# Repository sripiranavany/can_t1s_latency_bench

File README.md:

# CAN over Ethernet Latency Bench

A testbed for measuring latency when **CAN traffic is tunnelled over automotive
Ethernet**, built on Zephyr RTOS and STM32.

The aim is to quantify what it costs, in latency and jitter, to carry CAN frames
across single-pair Ethernet using IEEE 1722 / [Open1722](https://github.com/COVESA/Open1722)
(AVTP CAN encapsulation), compared with a native CAN bus. The matrix of
configurations to compare:

| | Classic CAN | CAN FD |
| --- | --- | --- |
| **10BASE-T1S** (PLCA multidrop) | Current focus | Planned |
| **100BASE-T1** (point-to-point) | Planned | Planned |

```
 CAN node ──CAN──▶ STM32 (Zephyr) ──SPI──▶ LAN8651 ══10BASE-T1S (PLCA)══ LAN8670 ──USB──▶ Linux host
                   bxCAN + OA-TC6           MAC-PHY                         EVB-LAN8670-USB   timestamps / analysis
```

## Technology stack

| Layer | Choice |
| --- | --- |
| RTOS | Zephyr |
| MCU | STM32 NUCLEO-F439ZI (bxCAN, classic CAN 2.0 only). A CAN FD capable MCU (FDCAN) is needed for the FD tests |
| Ethernet | 10BASE-T1S with PLCA, Microchip LAN8651 (MAC-PHY over SPI, OA TC6). 100BASE-T1 planned |
| CAN transport | IEEE 1722 AVTP via Open1722 |
| CAN PHY | MCP2562FD transceiver, PESD2CAN protection |
| Host | Linux (Raspberry Pi / PC) with EVB-LAN8670-USB, `microchip_t1s` driver |

## Status

| Item | State |
| --- | --- |
| SPI link STM32 ↔ Click Shield verified | Done |
| LAN8651 bring-up on Zephyr (direct wiring and Click Shield socket 3) | Done |
| 10BASE-T1S frames received on STM32 and bridged out on CAN1 | Working prototype (fixed CAN ID `0x123`) |
| Linux host PLCA setup (driver build, hotplug automation) | Done |
| Custom CAN SPE carrier PCB | Schematic and layout in progress |
| Open1722 (AVTP CAN) integration | Not started |
| CAN FD tests | Planned, needs an FDCAN-capable board |
| 100BASE-T1 tests | Planned, needs a 100BASE-T1 PHY / board |
| Latency measurement and analysis | Not started |

## Repository layout

| Path | Contents |
| --- | --- |
| [`host-tools/with-click-shield/`](host-tools/with-click-shield/) | Zephyr firmware for the NUCLEO-F439ZI: LAN8651 bring-up, raw-frame RX, CAN bridge. Wiring variants are selected with devicetree overlays |
| [`host-tools/t1s-plca-setup/`](host-tools/t1s-plca-setup/README.md) | udev rules, systemd unit and scripts that put an EVB-LAN8670-USB into a PLCA-configured state on boot and hotplug |
| [`hardware/CAN SPE CARRIER/`](hardware/CAN%20SPE%20CARRIER/README.md) | KiCad project for the carrier board (CAN transceiver + 10BASE-T1S on a Nucleo-144 / click-shield footprint) |
| [`hardware/kicad-files/`](hardware/kicad-files/) | Third-party KiCad parts (MCP2562FD, PESD2CAN) |
| [`docs/`](docs/) | Bring-up notes, see below |

## Documentation

- [Direct LAN8651 ↔ STM32F439ZI wiring](docs/direct-lan8651-stm32f439zi.md): the known-good hardware setup, plus the Click Shield route
- [SPI verification on the Click Shield](docs/spi-verification-click-shield.md): loopback test and pin mapping
- [10BASE-T1S on Linux](docs/t1s-driver-build.md): building the PHY driver and manual PLCA testing
- [Useful links](docs/links): Click Shield and Nucleo-144 datasheets

## Getting started

Prerequisites: a Zephyr SDK and `west` workspace, a NUCLEO-F439ZI, a MikroE
Two-Wire ETH Click (LAN8651), and a Linux host with an EVB-LAN8670-USB.

1. **Host side.** Build the `microchip_t1s` driver and set up PLCA, following
   [`docs/t1s-driver-build.md`](docs/t1s-driver-build.md) and then
   [`host-tools/t1s-plca-setup`](host-tools/t1s-plca-setup/README.md).
2. **Wire the Click board** to the Nucleo as described in
   [`docs/direct-lan8651-stm32f439zi.md`](docs/direct-lan8651-stm32f439zi.md).
3. **Build and flash the firmware:**

   ```bash
   cd host-tools/with-click-shield
   west build -b nucleo_f439zi -p always .
   west flash
   ```

   To use the Click Shield and/or the CAN bridge, stack overlays:

   ```bash
   west build -b nucleo_f439zi -p always . \
       -DEXTRA_DTC_OVERLAY_FILE="click-shield.overlay;can.overlay"
   ```

   The CAN overlay uses PD0 (RX) / PD1 (TX) and needs an external CAN
   transceiver. See the header of [`can.overlay`](host-tools/with-click-shield/can.overlay).

## Notes

- bxCAN on the STM32F4 is classic CAN 2.0 only (8-byte payload, 1 Mbit/s max). There is no CAN FD on this part, so the CAN FD runs will need a different MCU with FDCAN.
- Click Shield socket 3 needs its logic-level switch set to 3V3.
- `_backup/` holds an older EVB-LAN8670 setup guide kept for reference.

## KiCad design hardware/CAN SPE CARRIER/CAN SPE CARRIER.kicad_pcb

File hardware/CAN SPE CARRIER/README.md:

# CAN SPE CARRIER – PCB Routing Guide (for KiCad beginners)

This file explains **how the board was routed**, **what you are looking at when you open it in KiCad**,
and **what to check before sending it to a manufacturer**.

> **Fixed parts:** J3, J4, J5 and J6 are the click-shield / mainboard headers. Their positions were
> **not allowed to change**, so everything else was placed and routed around them.

---

## 1. Files in this folder

| File | What it is |
|---|---|
| `CAN SPE CARRIER.kicad_pro` | Project file (design rules, net classes) |
| `CAN SPE CARRIER.kicad_sch` | Schematic |
| `CAN SPE CARRIER.kicad_pcb` | The routed board – **open this one** |
| `CAN SPE CARRIER-backups/` | Automatic zip backups. `…-before-routing.kicad_pcb` is your board **before** the re-route |
| `_autosave-*.kicad_pcb` | KiCad autosave, safe to ignore/delete |
| `~*.lck` | Lock files from an earlier session. KiCad may warn "file is open" – if KiCad is not running, click *Ignore/Open anyway* or delete the `.lck` files |

---

## 2. Quick glossary

- **Net** – a set of pads that must be electrically connected (e.g. `GND`, `+3V3`, `/SPI_SCK`).
- **Track / trace** – a copper line that carries a net.
- **Via** – a plated hole that moves a track from one copper layer to the other.
- **Pad** – the copper spot on a part where you solder.
- **Zone / pour** – a big filled copper area (here: ground).
- **Net class** – a group of nets that share rules (track width, clearance). Here: `Default` and `Power`.
- **Ratsnest** – thin straight lines in KiCad showing connections that are *not yet routed*. A finished board has none.
- **DRC** – Design Rule Check; KiCad's automatic error checker.

---

## 3. Why the colours look different in KiCad

KiCad draws each copper layer in its own colour. If you opened the board and everything "changed colour", this is normal:

| Colour (default theme) | Layer | Meaning |
|---|---|---|
| **Red** | `F.Cu` | Front copper (top side) |
| **Green/Blue** | `B.Cu` | Back copper (bottom side) |
| Light red/green haze | GND zones | The ground pour on each layer |
| Yellow lines | `Edge.Cuts` | Board outline |

Tips:
- **Active layer is bright, the other layers are dimmed.** Press `PgUp` / `PgDn`, or click a layer in the
  right-hand *Appearance* panel, and the colours swap emphasis. That is why the board looks different each time.
- *Appearance* panel → **Layers** → *Colour* swatch lets you change any colour.
- **Highlight a net:** press `` ` `` (backtick) or use *Route → Highlight Net* (shortcut `` ` ``)
  and click a track. Everything on that net lights up, and everything else dims. This is the **best way to
  understand the routing**.
- *Appearance* → **Objects** → untick *Zones* (or set *Zone fill* opacity low) to hide the ground pour so you
  can see the tracks clearly.
- *Appearance* → **Nets** lets you show/hide or recolour individual nets.
- Press `B` to refill zones after any change; `Ctrl+B` clears the fill.
- **Show the whole board:** `Home`. **Zoom:** scroll wheel. **Measure:** `Ctrl+Shift+M`.

---

## 4. Board overview

```
                    TOP EDGE  (y ≈ 46…50 mm)
   J5 (left, x≈22)  ─────────────────────────  J6 (right, x≈85)
   click-shield side                              mainboard side
        │   J3 (x≈59, y≈73)    J4 (x≈59, y≈50)    │
        │   TP1 D1 R3 R2 C4  ← 3V3 loads           │
        │   C3  TP2          ← 5V cap              │
        │                                          │
        │   C2 C1  U2 (MCP2562 CAN transceiver)    │
        │                       D2  R1  J2   J1    │
        └──────────── BOTTOM (y ≈ 140 mm) ─────────┘
```

Roughly 69 × 93 mm board, 2 copper layers.

Signal flow in one sentence: **mainboard (J6→J4) and click shield (J5→J3) feed the CAN transceiver U2, whose CANH/CANL
outputs go through the protection diode D2 and termination R1 to the screw terminal J1 (and jumper J2).**

---

## 5. Routing, net by net

Track widths: signals **0.25 mm**, power **0.5 mm**, short stubs near pads 0.3 mm.
Clearance everywhere: **0.2 mm**. Vias: **0.6 mm pad / 0.3 mm drill**.

### 5.1 SPI bus (J5 → J3)
| Net | Layer | How |
|---|---|---|
| `/SPI_SCK` | F.Cu (top) | Part of a parallel bundle |
| `/SPI_MISO` | F.Cu (top) | Part of a parallel bundle |
| `/SPI_CS` | F.Cu (top) | Part of a parallel bundle |
| `/SPI_MOSI` | **B.Cu (bottom)** | Runs underneath the bundle |

- The three top-layer signals run side by side using **45° bends** (no sharp 90° corners), keeping the same spacing.
- MOSI was put on the **other layer** so it never has to cross the others → **no vias needed** for SPI.

### 5.2 Mainboard signals (J6 → J4): `/MB_INT`, `/MB_SCL`, `/MB_SDA`
- All on **F.Cu**, running along the **top edge** (above the headers).
- Each one sits at a **different height ("staggered levels")** so the lines never cross each other.
- In KiCad: highlight `/MB_INT` and you will see a long horizontal line at y ≈ 47.2 mm joining J6 to J4.

### 5.3 `/MB_RST`
- On **B.Cu** (bottom). It goes **around the right end of J3** and then up into pin **J3.2**.
- Using the back layer avoids all the top-layer signals.

### 5.4 +3V3 power
- A **0.5 mm trunk on F.Cu** from **J5.16** to **J3.7**, with short branches to the nearby 3.3 V parts
  (R2, R3, D1/LED resistor, C4, TP1).
- **One via** drops the net to **B.Cu**, and a short bottom run feeds **U2** (CAN transceiver VIO) and **C1** (100 nF decoupling).

### 5.5 +5V power
- A **0.5 mm trunk on F.Cu** to **J4.7** and **C3** (5 V bulk cap, placed right beside the trunk).
- A **B.Cu run goes straight down** to **U2** (VCC) and **C2** (100 nF decoupling).
- One via connects the top trunk to the bottom run.

### 5.6 CAN logic: `/CAN_TX`, `/CAN_RX`
- Direct, short **F.Cu** tracks from the J5 header down to U2 (TXD / RXD pins). No vias.

### 5.7 CAN bus: CANH / CANL
These are named `Net-(J1-Pin_1)` and `Net-(J1-Pin_2)` in KiCad (no custom label).
- Routed as a **matched pair** on F.Cu above J1: same layer, same length-ish, constant spacing.
- They are arranged so they **do not cross** each other on the way to D2 (ESD protection), R1 (120 Ω termination) and J1.
- Good practice for CAN: keep the pair together and symmetrical – that is what was done here.

### 5.8 Ground (GND)
- A **ground pour (zone) on both F.Cu and B.Cu** covering the whole board.
- Every GND pad connects into the pour (thermal-relief spokes: 0.4 mm bridges, 0.3 mm gap).
- **Vias join the top and bottom pours** so both are one ground. (The board currently has only 2 GND vias – see §8.)
- Because of the pour, you do not see individual GND tracks; ground is "everywhere there is no other signal".

---

## 6. Parts that were moved (none of J3–J6)

R1, R2, R3, C1, C3, C4, D1, D2, J2, TP1, TP2.

Why:
- **3.3 V loads** (R2, R3, C4, D1, C1) were moved next to the 3V3 trunk → shorter, simpler power tracks.
- **5 V cap** (C3) moved beside the 5V trunk.
- **D2, R1, J2** were moved **below J1**, because the body of the J1 screw terminal covered their old position.
- ⚠ **Check:** if the wires enter J1 from the **top** side, make sure D2, R1 and J2 don't block the wire entry.

---

## 7. Other changes made
- Added a **`Power` net class** in the project: **0.5 mm** tracks for `+5V` and `+3V3`
  (Board Setup → Design Rules → Net Classes).
- Old routing removed (it had 5 warnings, 8 unconnected items, dangling B.Cu tracks with no vias,
  long diagonal runs and no ground pour) and re-routed from scratch.
- Previous board saved as `CAN SPE CARRIER-backups/CAN SPE CARRIER-before-routing.kicad_pcb`
  (use *File → Restore Local Backup…* or just open that file).

---

## 8. How to review it yourself (step by step)

1. Open `CAN SPE CARRIER.kicad_pcb` (from the project, via the PCB Editor).
2. Press `B` to refill zones.
3. Run **Inspect → Design Rules Checker → Run DRC**. Expected: 0 errors, 0 unconnected items.
   (Tick *"Test for parity between PCB and schematic"* too.)
4. Walk through the nets: press `` ` `` on each track and read the list in §5.
5. Use **View → 3D Viewer** (`Alt+3`) to check that parts don't collide with J1.
6. Use *Appearance → Layers* to view only `F.Cu`, then only `B.Cu`.

### Things to improve / double-check
- **Stitching vias:** only 2 GND vias exist. Adding a few more near the edges and next to the signal vias
  (*Place → Via*, set net to `GND`) improves return-current paths between the two ground pours.
- **Check the current rating:** 0.5 mm copper at 1 oz handles roughly 1 A; verify this is enough for your 3V3 and 5V loads.
- **Fab capabilities:** the design uses 0.2 mm clearance, 0.25 mm signal tracks and 0.6/0.3 mm vias.
  Confirm your manufacturer allows these (most standard 2-layer services do).
- **Lock files:** delete `~*.lck` if KiCad keeps warning you.

---

## 9. Handy KiCad shortcuts (PCB Editor)

| Key | Action |
|---|---|
| `` ` `` | Highlight net under cursor |
| `B` | Refill all zones |
| `X` | Start routing a track |
| `V` | Place a via while routing (also switches layer) |
| `D` | Drag a track |
| `M` / `G` | Move / Grab (keeps connections) |
| `Del` | Delete selected |
| `Ctrl+Z` | Undo |
| `PgUp/PgDn` | Switch active copper layer |
| `Alt+3` | 3D viewer |
| `Ctrl+Shift+M` | Measure tool |
| `Home` | Zoom to fit |

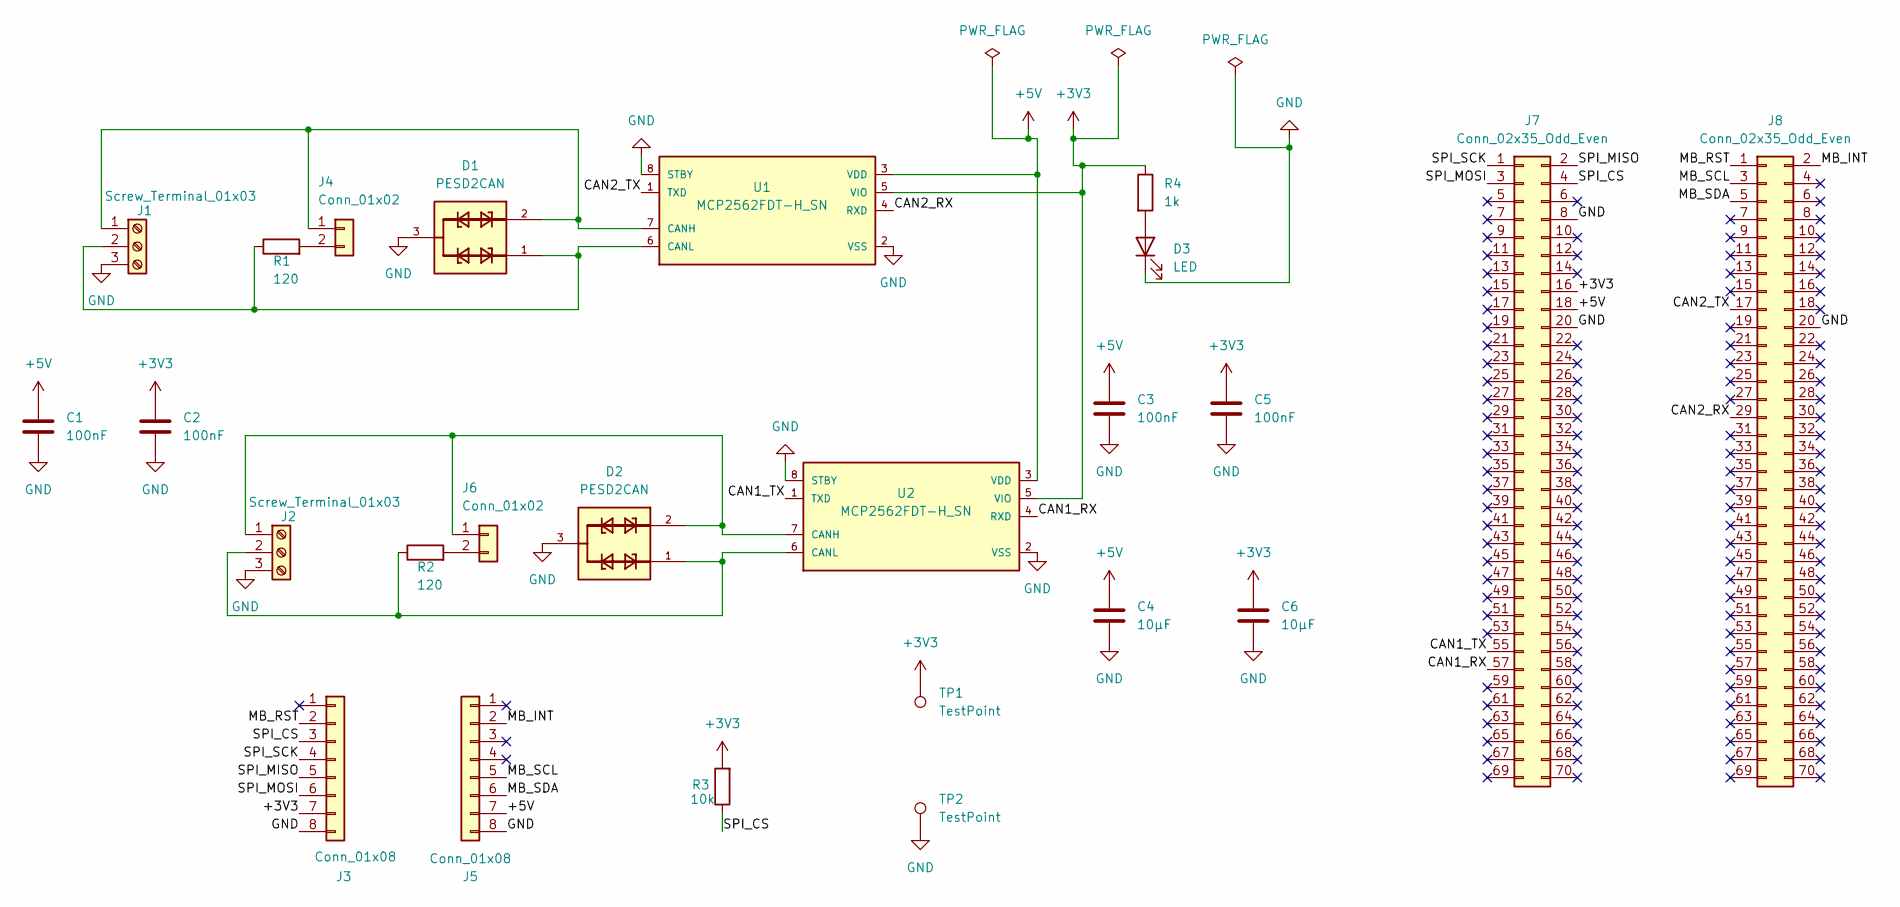
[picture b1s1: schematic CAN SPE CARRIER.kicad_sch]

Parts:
C1, C2, C3, C5: 100nF; C_0805_2012Metric
C4, C6: 10µF; C_0805_2012Metric
D1, D2: PESD2CAN; SOT-23
D3: LED; LED_0805_2012Metric
J1, J2: Screw_Terminal_01x03; TerminalBlock_Phoenix_MKDS-1,5-3-5.08_1x03_P5.08mm_Horizont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
J3, J5: Conn_01x08; PinSocket_1x08_P2.54mm_Vertical
J4, J6: Conn_01x02; PinHeader_1x02_P2.54mm_Vertical
J7, J8: Conn_02x35_Odd_Even; PinSocket_2x35_P2.54mm_Vertical
R1, R2: 120; R_0805_2012Metric
R3: 10k; R_0805_2012Metric
R4: 1k; R_0805_2012Metric
TP1, TP2: TestPoint; TestPoint_Pad_D1.5mm
U1, U2: MCP2562FDT-H_SN; SOIC-8_3.9x4.9mm_P1.27mm

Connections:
+3V3: C2.1, C5.1, C6.1, J3.7, J7.16, R3.2, R4.1, TP1.1 (1_1), U1.5 (VIO), U2.5 (VIO)
+5V: C1.1, C3.1, C4.1, J5.7, J7.18, U1.3 (VDD), U2.3 (VDD)
/CAN1_RX: J7.57, U2.4 (RXD)
/CAN1_TX: J7.55, U2.1 (TXD)
/CAN2_RX: J8.29, U1.4 (RXD)
/CAN2_TX: J8.17, U1.1 (TXD)
/MB_INT: J5.2, J8.2
/MB_RST: J3.2, J8.1
/MB_SCL: J5.5, J8.3
/MB_SDA: J5.6, J8.5
/SPI_CS: J3.3, J7.4, R3.1
/SPI_MISO: J3.5, J7.2
/SPI_MOSI: J3.6, J7.3
/SPI_SCK: J3.4, J7.1
GND: C1.2, C2.2, C3.2, C4.2, C5.2, C6.2, D1.3, D2.3, D3.1 (K), J1.3, J2.3, J3.8, J5.8, J7.8, J7.20, J8.20, TP2.1 (1_1), U1.2 (VSS), U1.8 (STBY), U2.2 (VSS), U2.8 (STBY)
unnamed: D3.2 (A), R4.2
unnamed: D1.2, J1.1, J4.1, U1.7 (CANH)
unnamed: D1.1, J1.2, R1.1, U1.6 (CANL)
unnamed: D2.2, J2.1, J6.1, U2.7 (CANH)
unnamed: D2.1, J2.2, R2.1, U2.6 (CANL)
unnamed: J4.2, R1.2
unnamed: J6.2, R2.2

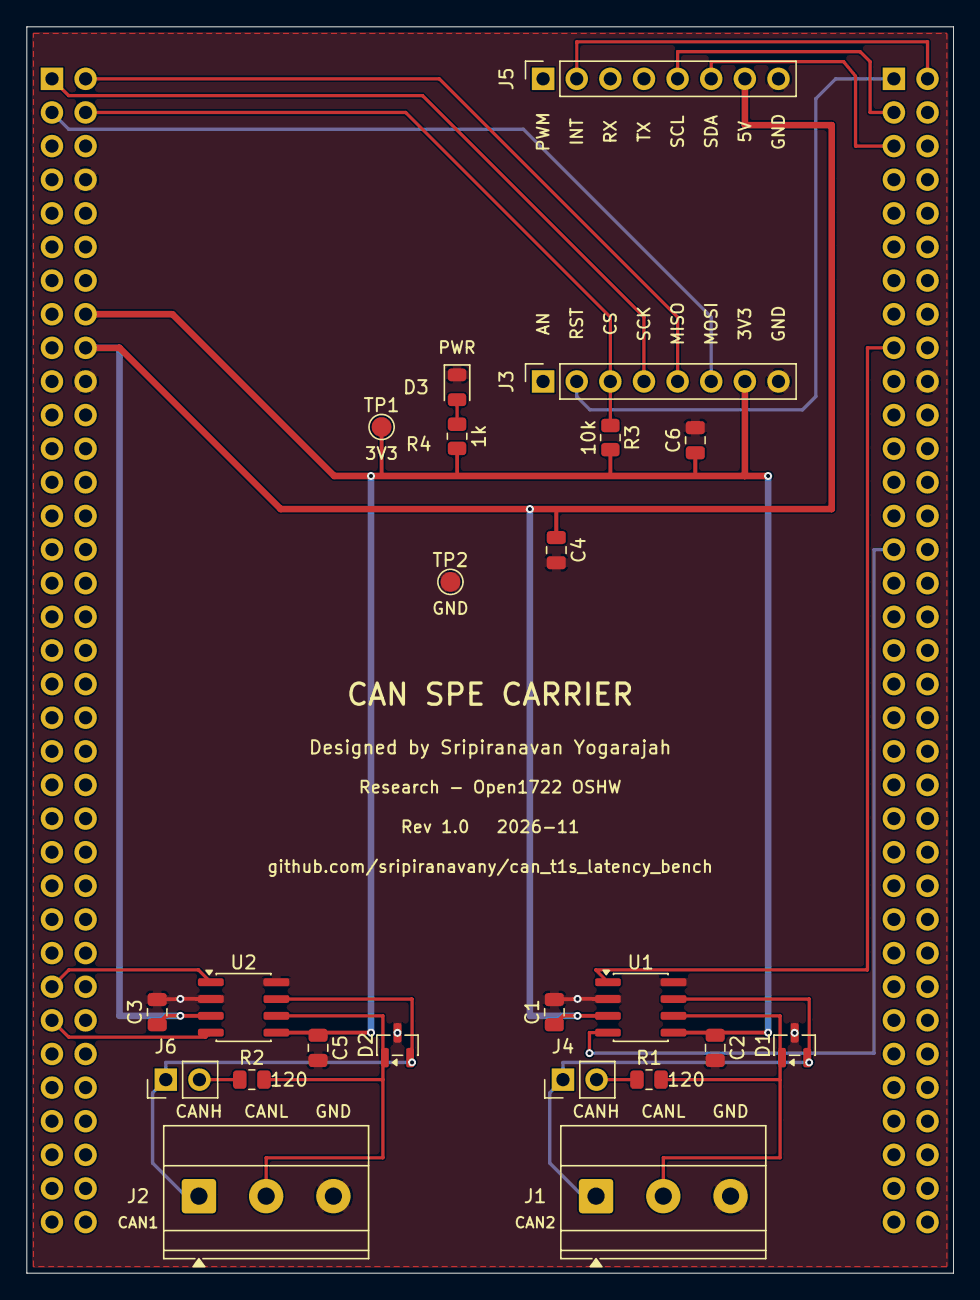
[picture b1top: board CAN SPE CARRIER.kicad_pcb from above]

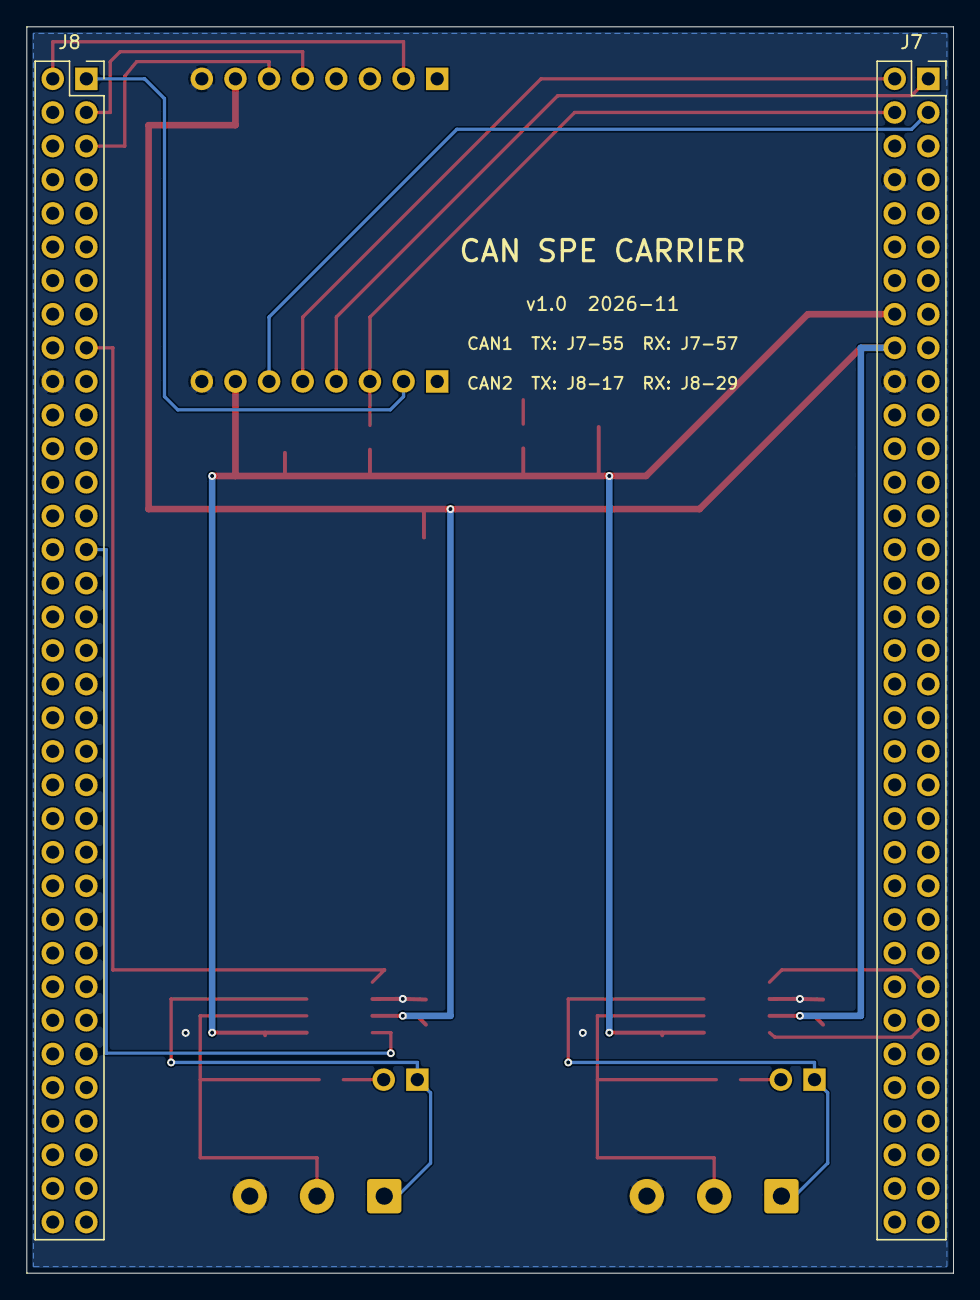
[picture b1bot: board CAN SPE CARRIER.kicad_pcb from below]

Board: 2 copper layers, 70.0 x 94.2 mm, 25 parts (2 on the bottom side), 22 nets.
